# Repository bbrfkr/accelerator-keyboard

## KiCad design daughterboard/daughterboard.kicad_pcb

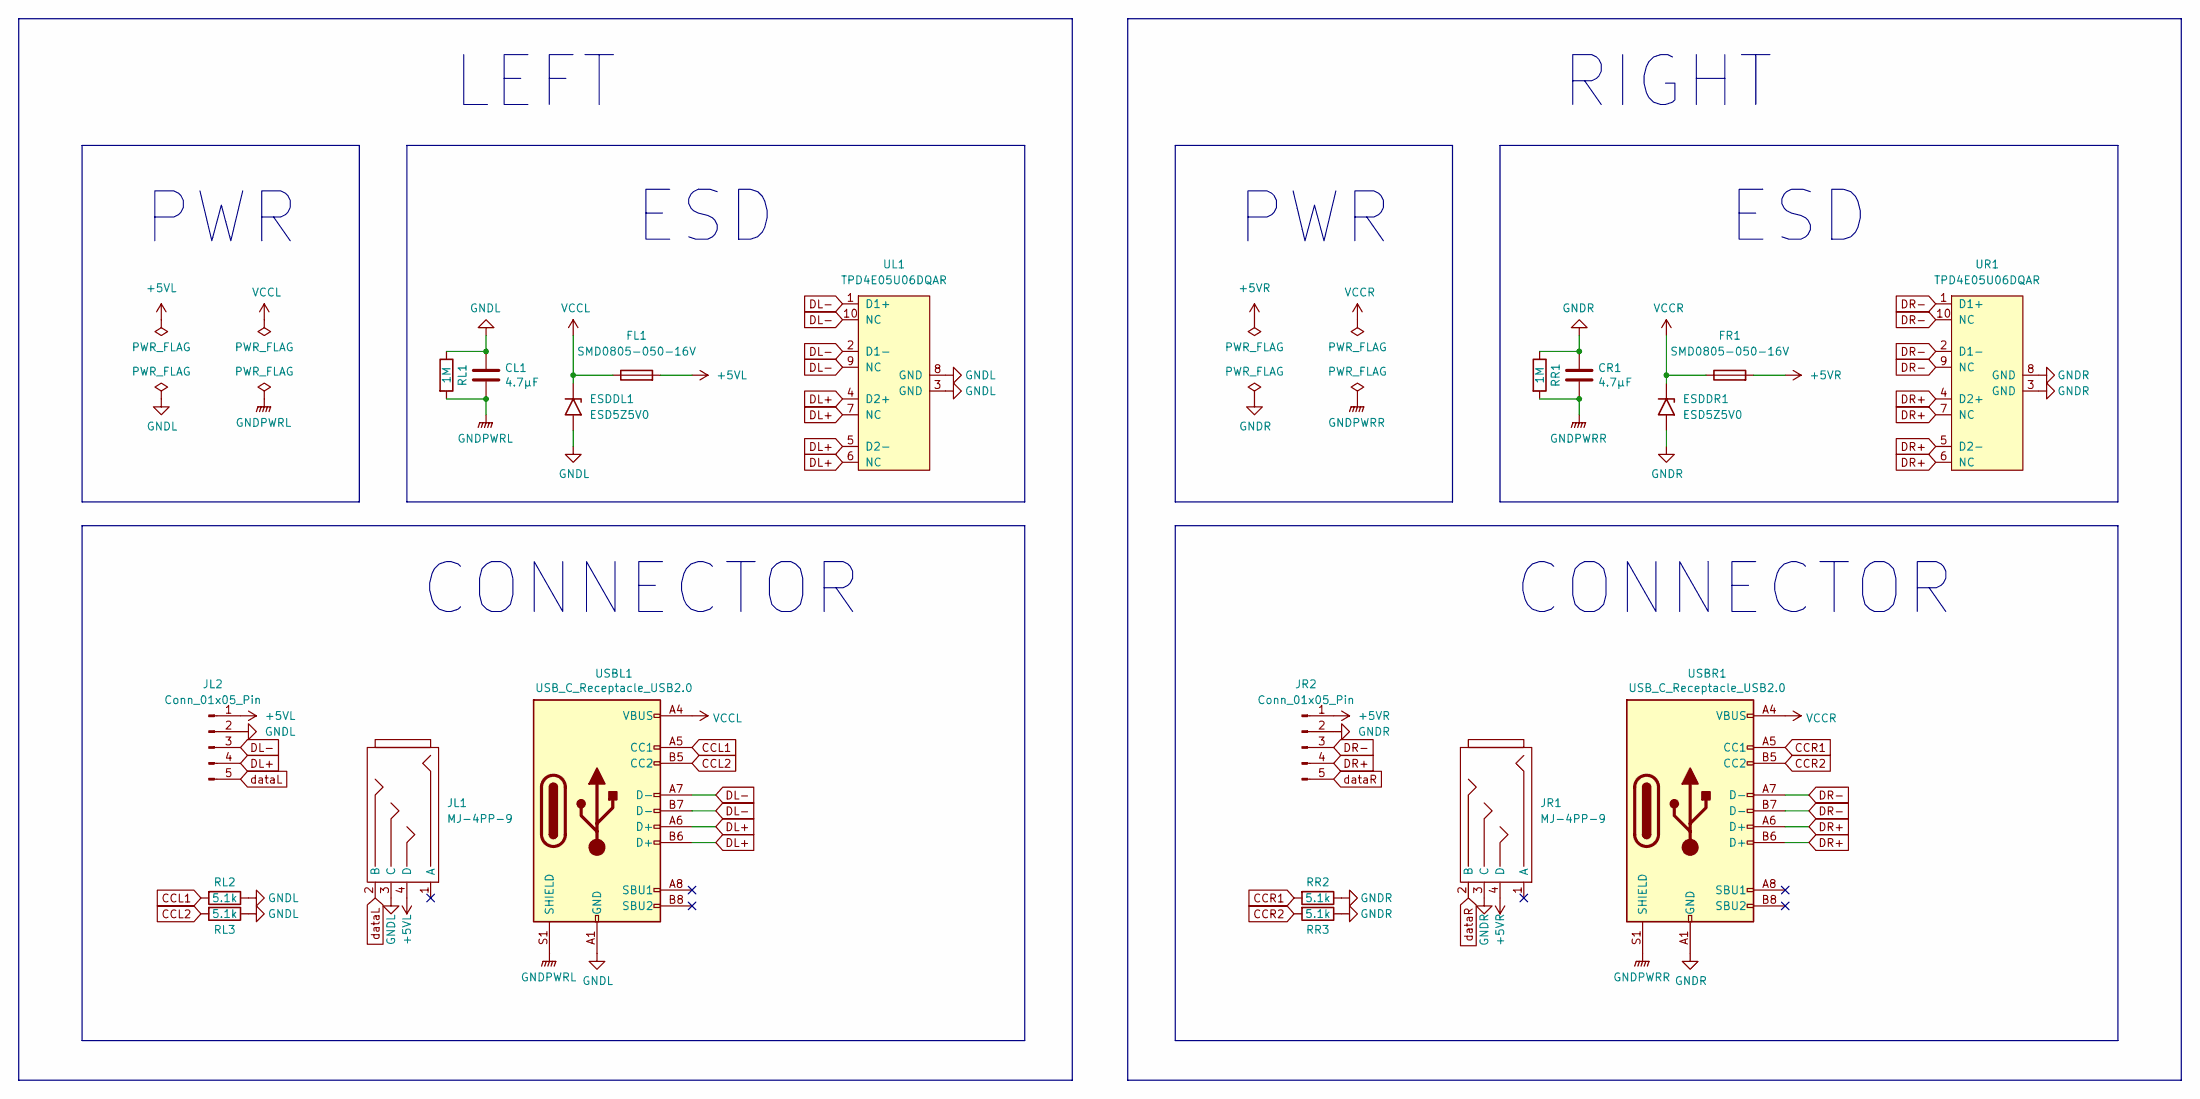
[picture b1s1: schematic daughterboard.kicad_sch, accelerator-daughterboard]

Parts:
CL1: 4.7μF; C_1206_3216Metric; LCSC C29823
CR1: 4.7μF; C_1206_3216Metric; LCSC C29823
ESDDL1: ESD5Z5V0; D_SOD-523; Manufacturer Part Number ESD5Z5V0; LCSC C502546
ESDDR1: ESD5Z5V0; D_SOD-523; Manufacturer Part Number ESD5Z5V0; LCSC C502546
FL1: SMD0805-050-16V; Fuse_1206_3216Metric; Manufacturer Part Number SMD0805-050-16V; LCSC C2833485
FR1: SMD0805-050-16V; Fuse_1206_3216Metric; Manufacturer Part Number SMD0805-050-16V; LCSC C2833485
JL1: MJ-4PP-9
JL2: Conn_01x05_Pin; JST_PH_S5B-PH-K_1x05_P2.00mm_Horizontal
JR1: MJ-4PP-9
JR2: Conn_01x05_Pin; JST_PH_S5B-PH-K_1x05_P2.00mm_Horizontal
RL1: 1M; R_1206_3216Metric; LCSC C2759631
RL2, RL3: 5.1k; R_1206_3216Metric; LCSC C964991
RR1: 1M; R_1206_3216Metric; LCSC C2759631
RR2, RR3: 5.1k; R_1206_3216Metric; LCSC C964991
UL1: TPD4E05U06DQAR; USON-10_L2.5-W1.0-P0.50-BL; LCSC C2836386
UR1: TPD4E05U06DQAR; USON-10_L2.5-W1.0-P0.50-BL; LCSC C2836386
USBL1: USB_C_Receptacle_USB2.0; USB_C_Receptacle_HRO_TYPE-C-31-M-12; LCSC C165948
USBR1: USB_C_Receptacle_USB2.0; USB_C_Receptacle_HRO_TYPE-C-31-M-12; LCSC C165948

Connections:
+5VL: FL1.2, JL1.4 (D), JL2.1
+5VR: FR1.2, JR1.4 (D), JR2.1
CCL1: RL2.2, USBL1.A5 (CC1)
CCL2: RL3.2, USBL1.B5 (CC2)
CCR1: RR2.2, USBR1.A5 (CC1)
CCR2: RR3.2, USBR1.B5 (CC2)
DL+: JL2.4, UL1.4 (D2+), UL1.5 (D2-), UL1.6 (NC), UL1.7 (NC), USBL1.A6 (D+), USBL1.B6 (D+)
DL-: JL2.3, UL1.1 (D1+), UL1.2 (D1-), UL1.9 (NC), UL1.10 (NC), USBL1.A7 (D-), USBL1.B7 (D-)
DR+: JR2.4, UR1.4 (D2+), UR1.5 (D2-), UR1.6 (NC), UR1.7 (NC), USBR1.A6 (D+), USBR1.B6 (D+)
DR-: JR2.3, UR1.1 (D1+), UR1.2 (D1-), UR1.9 (NC), UR1.10 (NC), USBR1.A7 (D-), USBR1.B7 (D-)
GNDL: CL1.1, ESDDL1.2 (A2), JL1.3 (C), JL2.2, RL1.1, RL2.1, RL3.1, UL1.3 (GND), UL1.8 (GND), USBL1.A1 (GND), USBL1.A12 (GND), USBL1.B1 (GND), USBL1.B12 (GND)
GNDPWRL: CL1.2, RL1.2, USBL1.S1 (SHIELD)
GNDPWRR: CR1.2, RR1.2, USBR1.S1 (SHIELD)
GNDR: CR1.1, ESDDR1.2 (A2), JR1.3 (C), JR2.2, RR1.1, RR2.1, RR3.1, UR1.3 (GND), UR1.8 (GND), USBR1.A1 (GND), USBR1.A12 (GND), USBR1.B1 (GND), USBR1.B12 (GND)
VCCL: ESDDL1.1 (A1), FL1.1, USBL1.A4 (VBUS), USBL1.A9 (VBUS), USBL1.B4 (VBUS), USBL1.B9 (VBUS)
VCCR: ESDDR1.1 (A1), FR1.1, USBR1.A4 (VBUS), USBR1.A9 (VBUS), USBR1.B4 (VBUS), USBR1.B9 (VBUS)
dataL: JL1.2 (B), JL2.5
dataR: JR1.2 (B), JR2.5

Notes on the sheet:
LEFT
PWR
RIGHT
ESD
CONNECTOR

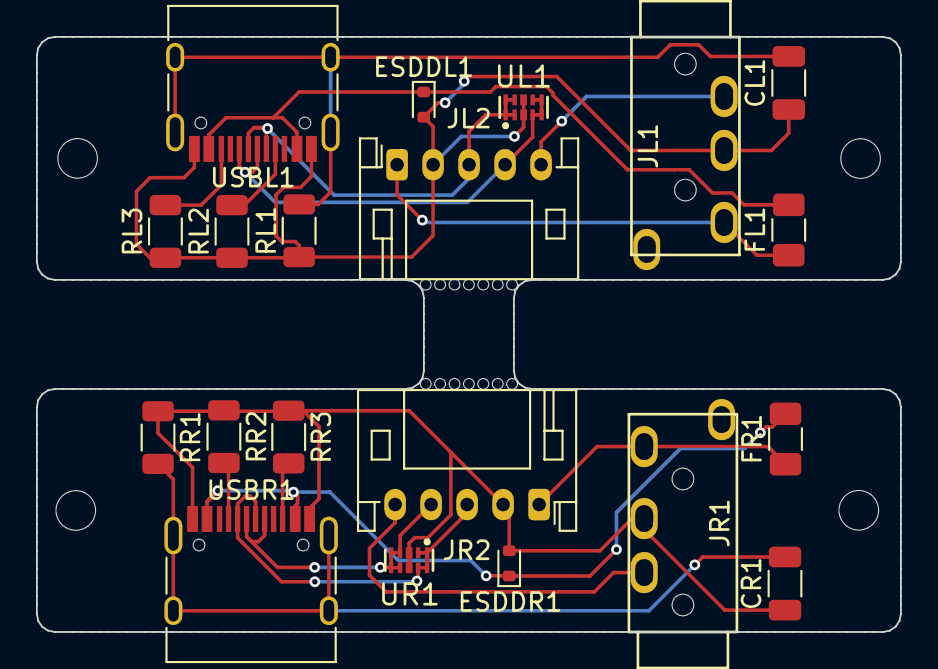
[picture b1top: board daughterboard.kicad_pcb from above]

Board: 2 copper layers, 48.0 x 33.1 mm, 26 parts (0 on the bottom side), 18 nets.

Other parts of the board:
HOLE01, HOLE02, HOLE03, HOLE04: MountingHole_2.2mm_M2
HOLE05, HOLE06: bites; mousebites
